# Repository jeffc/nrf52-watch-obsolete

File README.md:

# nrf52-watch

## Overview

This repo is, at present, a work-in-progress playground for designing and
building a smartwatch based on the nrf52840 microcontroller from Nordic.

## Parts

  * [MS88SF2 nRF52840 Module](https://en.minewtech.com/bluetooth-module/MS88SF2.html)
    * Main brains. nRF52840 chipset chosen for BLE capability and low (&lt;1uA)
      sleep current.
    * Chosen for ease of solderability; other modules have pads that aren't
      accessible from the sides of the module.
  * [Sharp LS013B7DH03 1.28" Memory LCD](https://www.sharpsma.com/products?sharpCategory=Memory%20LCD&p_p_parallel=0&sharpProductRecordId=1504572)
    * Always-on display.
    * Chosen for size and small power consumption.
  * [DS1302 RTC](https://datasheets.maximintegrated.com/en/ds/DS1302.pdf)
    * Realtime clock, for real timekeeping.
    * Chosen for small power consumption and library support.

## Power

  * Project is planned to be powered by a [CR3032 coin cell](https://www.digikey.com/product-detail/en/panasonic-bsg/CR3032/P121-ND/107126),
    which has a nominal capacity of 500mAh at 3V.
  * Projected lifetime is &gt;2mo, though it remains to be seen if this is
    possible

## Software

  Since there isn't code written yet, this section is largely my notepad on
  ideas and framework setup.

  * To conserve power, everything will be interrupts-driven. 
    * This includes a 60Hz toggle for the memory LCD's EXTCOMIN pin
  * PlatformIO doesn't have a builtin for the sparkfun dev board I'm using, so
    the packages/ directory and corresponding lines in platformio.ini are a
    workaround to keep the repository as portable as possible
  * A decent amount of build hackery was needed to make the native version build
    with the dummy adafruit_gfx library

## Credits / Inspiration

  * This project uses open-source code from the following projects. Licenses are
    included alongside code where applicable.
    * [Adafruit](https://github.com/adafruit/Adafruit-GFX-Library)
    * [vhervieux on github](https://github.com/croutor/Adafruit_GFX_dummy_display)
    * [jeraymond on github](https://github.com/jeraymond/pio-sparkfun_pro_nrf52840_mini-setup)
    * [UF2Conv from Microsoft](https://raw.githubusercontent.com/microsoft/uf2/master/utils/uf2conv.py)
  * This project took inspiration from these projects:
    * [Chronio](https://hackaday.io/project/12876-chronio)
    * [Samson March's Smartwatch](https://imgur.com/a/FSBwD3g)

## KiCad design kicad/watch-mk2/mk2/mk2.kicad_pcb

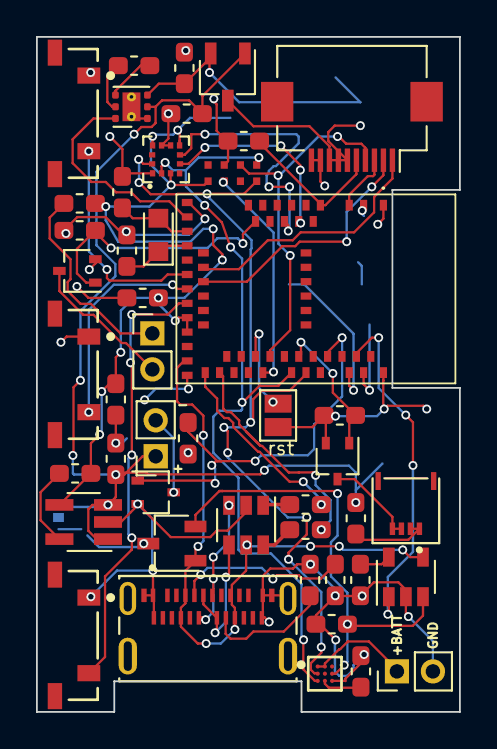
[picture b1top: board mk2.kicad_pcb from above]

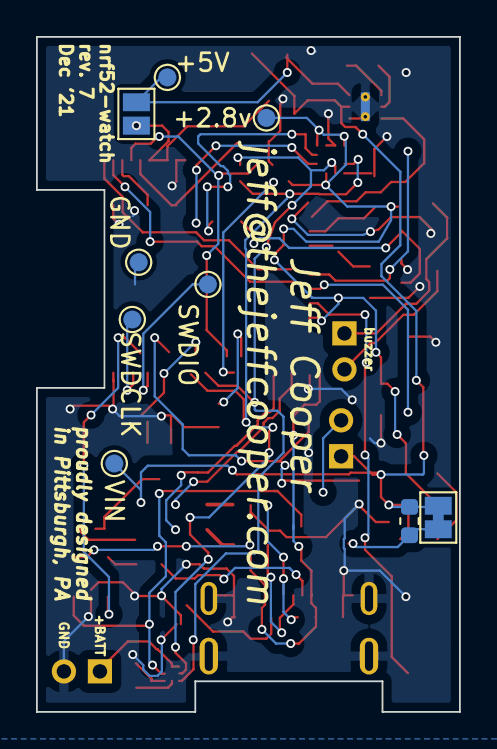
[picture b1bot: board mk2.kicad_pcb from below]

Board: 2 copper layers, 23.5 x 37.5 mm, 55 parts (9 on the bottom side), 50 nets.

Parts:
BT1: Battery_Cell; PinHeader_1x02_P2.00mm_Vertical
C1, C2: 12pF; C_0603_1608Metric_Pad1.05x0.95mm_HandSolder
C3, C7: 10uF; C_0603_1608Metric_Pad1.05x0.95mm_HandSolder
C4, C20: 4.7uF; C_0603_1608Metric_Pad1.05x0.95mm_HandSolder
C5, C6, C8: 2.2uF; C_0603_1608Metric_Pad1.05x0.95mm_HandSolder
C9: 560pF; C_0603_1608Metric_Pad1.05x0.95mm_HandSolder
C10: 0.47uF; C_0603_1608Metric_Pad1.05x0.95mm_HandSolder
D1, D2: D_Schottky_x2_KCom_AAK; TSOT-23
IC1: MDBT50Q; 113990582
IC2: M41T62LC6F; LCC90P230X50X80-8N
J1: Conn_01x10_Female; Hirose_FH12-10S-0.5SH_1x10-1MP_P0.50mm_Horizontal
J2: 2305018-2; TE_2305018-2
J3: Conn_01x02_Female; PinHeader_1x02_P2.00mm_Vertical
J4: 503480-0400; MOLEX_503480-0400
J6: Conn_01x02_Female; PinSocket_1x02_P2.00mm_Vertical
JP1, JP2: Jumper_NO_Small; SolderJumper-2_P1.3mm_Open_Pad1.0x1.5mm
JP3: Jumper_NC_Small; SolderJumper-2_P1.3mm_Bridged_Pad1.0x1.5mm
L1: 2.2uH; L_0603_1608Metric_Pad1.05x0.95mm_HandSolder
Q1, Q3, Q4: Si1308EDL; SOT-323_SC-70
R1: shunt; R_0603_1608Metric
R2, R13, R15: 100k; R_0603_1608Metric_Pad1.05x0.95mm_HandSolder
R3, R4: 27; R_0603_1608Metric_Pad1.05x0.95mm_HandSolder
R9: 2k; R_0603_1608Metric_Pad1.05x0.95mm_HandSolder
R11, R12: 5.1k; R_0603_1608Metric_Pad1.05x0.95mm_HandSolder
R14: 100; R_0603_1608Metric_Pad1.05x0.95mm_HandSolder
R16: 10; R_0603_1608Metric_Pad1.05x0.95mm_HandSolder
SW1: B5; E-Switch-TL3330AF130QG-MFG
SW2: B1; E-Switch-TL3330AF130QG-MFG
SW4: B3; E-Switch-TL3330AF130QG-MFG
TP1, TP2, TP3, TP4, TP5, TP6: TestPoint; TestPoint_Pad_D1.0mm
U1: TPS60151DRV; WSON-6-1EP_2x2mm_P0.65mm_EP1x1.6mm_ThermalVias
U2: LM3671MF-2.8_NOPB; SOT-23-5_HandSoldering
U3: MCP73831-2-OT; SOT-23-5
U4: BMA400; XDCR_BMA400
U5: TPD2S017; SOT-23-6
U6: MAX17262REWL+T; Maxim-W91G1-3-0-A-IPC_A
Y1: 32.768kHz; Crystal_SMD_2012-2Pin_2.0x1.2mm_HandSoldering

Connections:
5VREG_EN: IC1.16 (P0.27), U1.6 (ENA)
+5V: C8.1, D2.2 (A), JP1.2, TP6.1, U1.3 (VOUT)
+BATT: BT1.1 (+), U6.A1 (TH), U6.A2 (BATT)
/XL1: C1.2, IC1.17 (P0.00/XL1), Y1.2
/XL2: C2.2, IC1.18 (P0.01/XL2), Y1.1
ACCELINT1: IC1.7 (P1.14), U4.5 (INT1)
ACCELINT2: IC1.9 (P0.03), U4.6 (INT2)
BACKLIGHT: IC1.45 (P0.23), Q3.1 (G), R13.1
BATTPOW: C20.1, D1.2 (A), U3.3 (VBAT), U6.B3 (SYS)
BUTTON1: IC1.22 (P0.06), SW2.2
BUTTON3: IC1.26 (P1.09), SW4.2
BUTTON5: IC1.24 (P0.08), SW1.2
BUZZER: IC1.13 (P0.28), Q4.1 (G), R15.1
CHGNG: IC1.52 (P0.09/NFC1), U3.1 (STAT)
DISP_POWER: D2.3 (K), J1.6, J1.7, J1.8, JP1.1
FLASHLIGHT: IC1.49 (P0.25), Q1.1 (G), R2.1
GND: BT1.2 (-), C1.1, C2.1, C3.2, C4.2, C5.1, C7.2, C8.2, C9.2, C10.2, C20.2, IC1.1 (GND_1), IC1.2 (GND_2), IC1.15 (GND_3), IC1.33 (GND_4), IC1.55 (GND_5), IC2.3 (VSS), J1.9, J1.10, J2.A1 (GNDA), J2.A12 (GNDA__1), J2.B1 (GNDB), J2.B12 (GNDB__1), J2.G1 (GND), J2.G2 (GND__1), J2.S1 (SHIELD), J2.S2 (SHIELD__1), J2.S3 (SHIELD__2), J2.S4 (SHIELD__3), JP2.2, Q1.2 (S), Q3.2 (S), Q4.2 (S), R2.2, R9.2, R11.2, R12.1, R13.2, R15.2, SW1.1, SW2.1, SW4.1, TP1.1, U1.1 (GND), U1.7 (EP), U2.2 (GND), U3.2 (VSS), U4.1 (SDO), U4.8 (GNDIO), U4.9 (GND), U5.2 (GND), U6.C3 (GND)
LCD_CS: IC1.3 (P1.10), J1.3
LCD_DISP: C9.1, IC1.4 (P1.11), J1.5
unnamed: C6.1, U1.4 (CP+)
unnamed: C6.2, U1.5 (CP-)
unnamed: C10.1, U6.C2 (REG)
unnamed: D1.3 (K), JP3.2, R1.1
unnamed: IC1.34 (D-), R3.1
unnamed: IC1.35 (D+), R4.1
unnamed: J3.1, R16.2
unnamed: J3.2, Q4.3 (D)
unnamed: J4.1, J4.2, R14.2
unnamed: J4.3, J4.4, Q3.3 (D)
unnamed: J6.2, Q1.3 (D)
unnamed: L1.1, U2.5 (SW)
unnamed: R9.1, U3.5 (PROG)
unnamed: J2.B5 (CC2), R11.1
unnamed: J2.A5 (CC1), R12.2
RST: IC1.40 (P0.18/RESET), JP2.1
RTCIRQ: IC1.41 (P0.17), IC2.6 (~IRQ/OUT~)
SCL: IC1.46 (P0.22), IC2.8 (SCL), U4.12 (SCX), U6.B1 (SCL)
SDA: IC1.44 (P0.20), IC2.1 (SDA), U4.2 (SDX), U6.C1 (SDA)
SPI_CLK: IC1.21 (P0.05), J1.1
SPI_MOSI: IC1.23 (P0.07), J1.2
SQW: IC1.42 (P0.19), IC2.2 (SQW), J1.4
SWDCLK: IC1.53 (SWDCLK), TP2.1
SWDIO: IC1.51 (SWDIO), TP4.1
USB_DN: R3.2, U5.1 (CH1Out)
USB_DN_EXT: J2.A7 (DA_N), J2.B7 (DB_N), U5.3 (CH1In)
USB_DP: R4.2, U5.6 (CH2Out)
USB_DP_EXT: J2.A6 (DA_P), J2.B6 (DB_P), U5.4 (CH2Int)
VCC: C3.1, C7.1, IC1.28 (VDD), IC1.30 (VDDH), IC2.5 (VCC), L1.2, R16.1, TP3.1, U2.4 (FB), U4.3 (VDDIO), U4.7 (VDD), U4.10 (~CSB~)
VIN: C4.1, C5.2, D2.1 (A), J6.1, JP3.1, R1.2, R14.1, TP5.1, U1.2 (VIN), U2.1 (VIN), U2.3 (EN)
VUSB: D1.1 (A), IC1.32 (VBUS), J2.A4 (VBUS_A), J2.A9 (VBUS_A__1), J2.B4 (VBUS_B), J2.B9 (VBUS_B__1), U3.4 (VDD), U5.5 (VCC)

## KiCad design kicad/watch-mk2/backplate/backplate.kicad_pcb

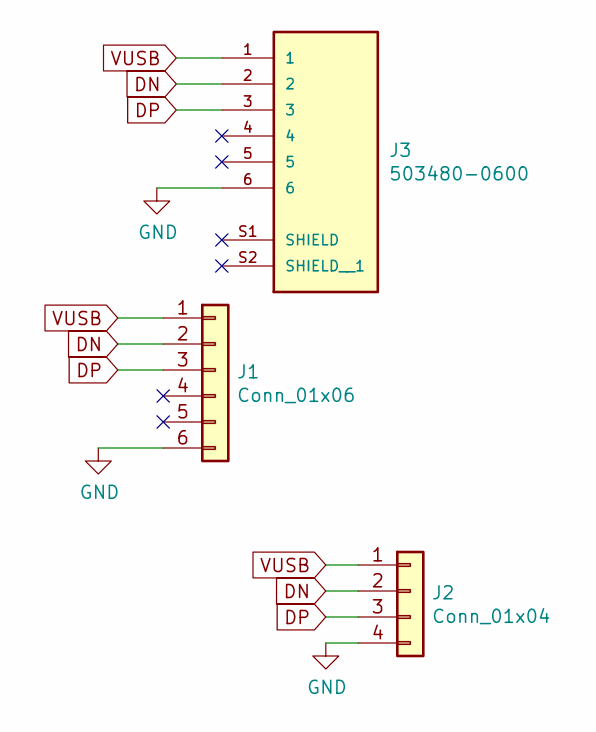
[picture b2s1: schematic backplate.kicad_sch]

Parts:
J1: Conn_01x06; ffc-strip
J2: Conn_01x04; PinHeader_1x04_P2.00mm_Vertical
J3: 503480-0600; MOLEX_503480-0600; PARTREV H

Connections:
DN: J1.2, J2.2, J3.2
DP: J1.3, J2.3, J3.3
GND: J1.6, J2.4, J3.6
VUSB: J1.1, J2.1, J3.1

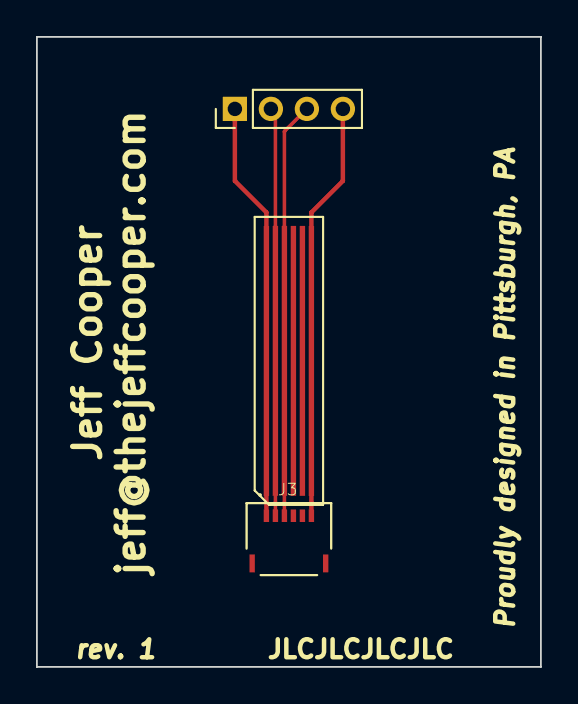
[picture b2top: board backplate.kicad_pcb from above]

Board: 2 copper layers, 28.0 x 35.0 mm, 3 parts (0 on the bottom side), 4 nets.

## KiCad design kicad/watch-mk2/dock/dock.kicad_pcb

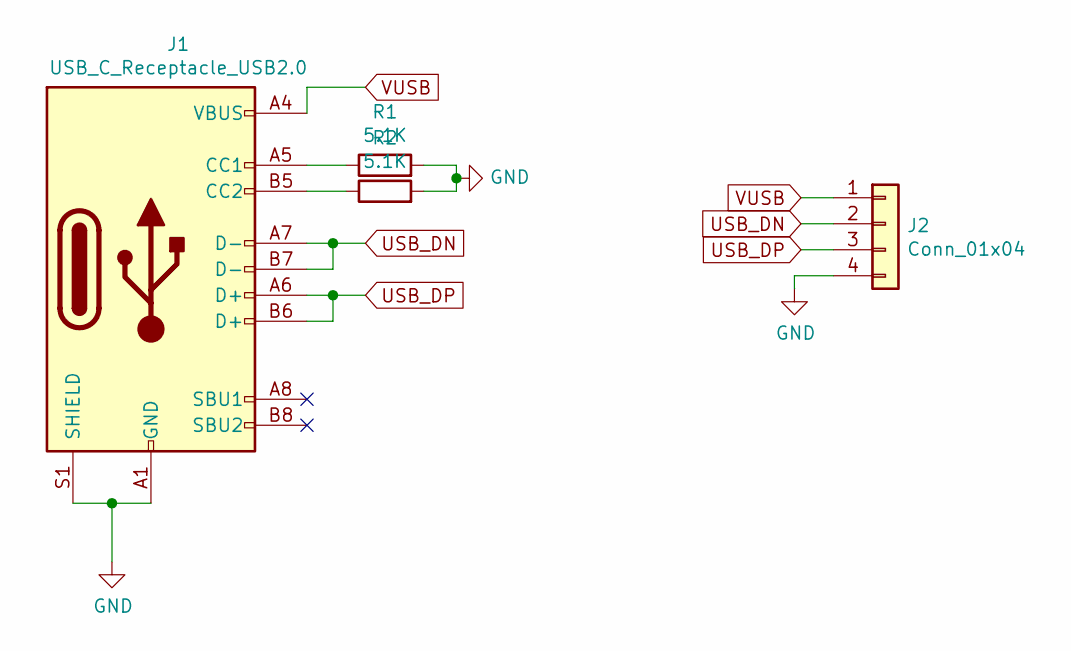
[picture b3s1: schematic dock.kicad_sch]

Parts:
J1: USB_C_Receptacle_USB2.0; USB_C_Receptacle_Palconn_UTC16-G
J2: Conn_01x04; pins
R1, R2: 5.1K; R_0603_1608Metric

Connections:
GND: J1.A1 (GND), J1.A12 (GND), J1.B1 (GND), J1.B12 (GND), J1.S1 (SHIELD), J2.4, R1.2, R2.2
unnamed: J1.A5 (CC1), R1.1
unnamed: J1.B5 (CC2), R2.1
USB_DN: J1.A7 (D-), J1.B7 (D-), J2.2
USB_DP: J1.A6 (D+), J1.B6 (D+), J2.3
VUSB: J1.A4 (VBUS), J1.A9 (VBUS), J1.B4 (VBUS), J1.B9 (VBUS), J2.1

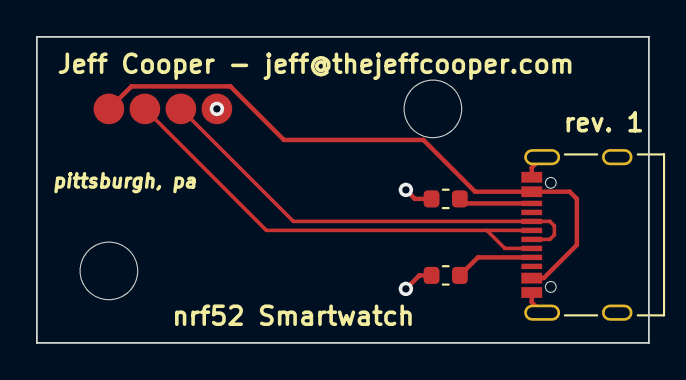
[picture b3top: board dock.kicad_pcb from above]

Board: 2 copper layers, 34.0 x 17.0 mm, 4 parts (0 on the bottom side), 6 nets.

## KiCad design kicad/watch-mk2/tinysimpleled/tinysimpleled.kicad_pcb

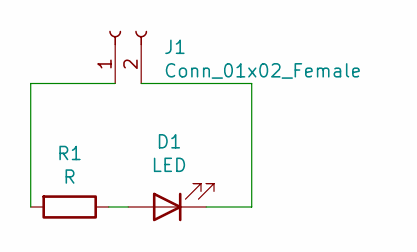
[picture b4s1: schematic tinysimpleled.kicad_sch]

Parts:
D1: LED; XM-L2
J1: Conn_01x02_Female; PinHeader_1x02_P1.00mm_Vertical
R1: R; R_2512_6332Metric

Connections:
unnamed: D1.1 (K), J1.2
unnamed: D1.2 (A), R1.1
unnamed: J1.1, R1.2

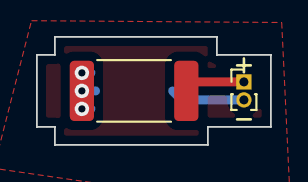
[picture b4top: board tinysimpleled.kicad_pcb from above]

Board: 2 copper layers, 13.0 x 6.0 mm, 3 parts (1 on the bottom side), 3 nets.

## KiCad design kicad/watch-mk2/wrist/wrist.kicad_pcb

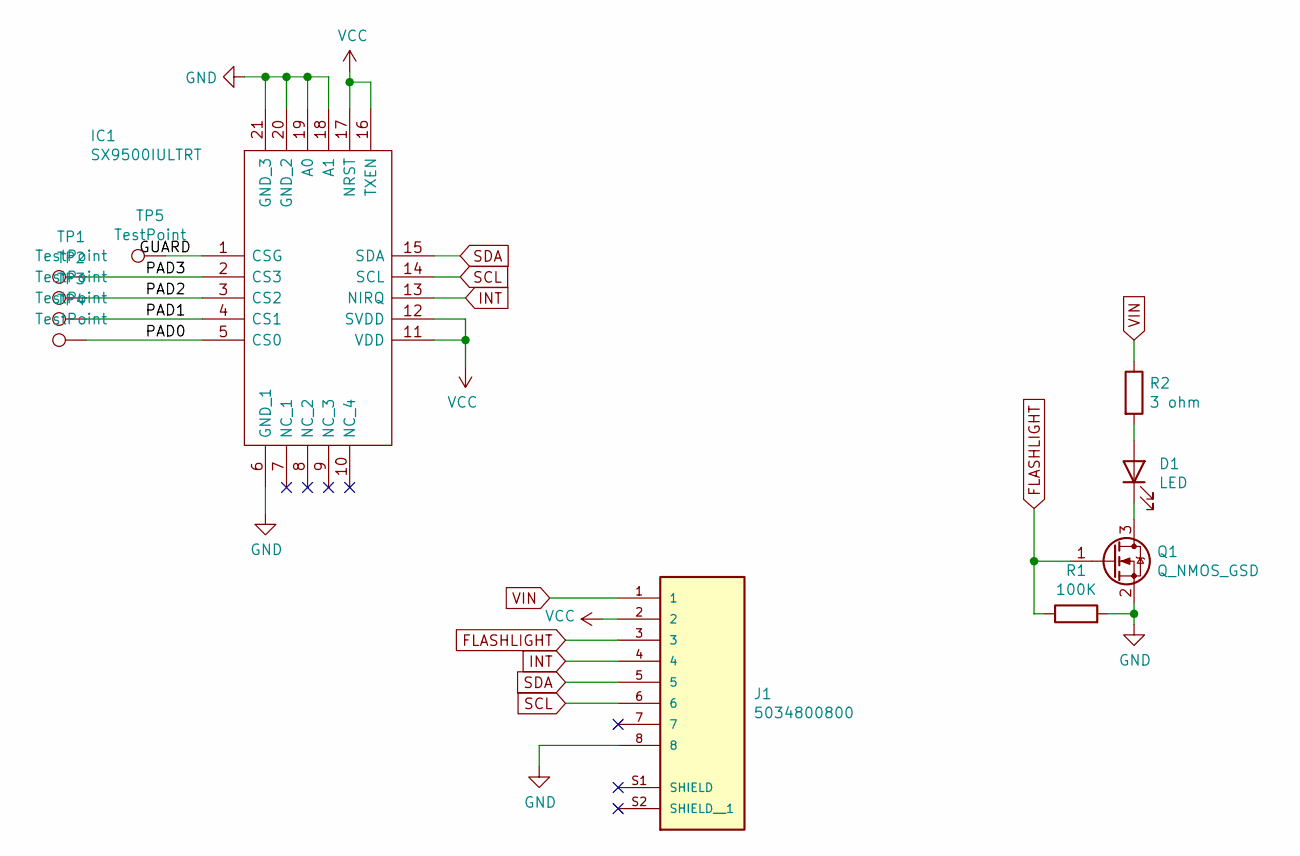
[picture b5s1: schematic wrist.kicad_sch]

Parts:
D1: LED; XM-L2
IC1: SX9500IULTRT; QFN40P300X300X60-21N; Manufacturer_Part_Number SX9500IULTRT; Mouser Part Number 947-SX9500IULTRT
J1: 5034800800; MOLEX_5034800800; PARTREV H
Q1: Q_NMOS_GSD; SOT-323_SC-70
R1: 100K; R_0603_1608Metric
R2: 3 ohm; R_2512_6332Metric
TP1, TP2, TP3, TP4, TP5: TestPoint; TestPoint_Pad_D4.0mm

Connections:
/GUARD: IC1.1 (CSG), TP5.1
/PAD0: IC1.5 (CS0), TP4.1
/PAD1: IC1.4 (CS1), TP3.1
/PAD2: IC1.3 (CS2), TP2.1
/PAD3: IC1.2 (CS3), TP1.1
FLASHLIGHT: J1.3, Q1.1 (G), R1.1
GND: IC1.6 (GND_1), IC1.18 (A1), IC1.19 (A0), IC1.20 (GND_2), IC1.21 (GND_3), J1.8, Q1.2 (S), R1.2
INT: IC1.13 (NIRQ), J1.4
unnamed: D1.1 (K), Q1.3 (D)
unnamed: D1.2 (A), R2.2
SCL: IC1.14 (SCL), J1.6
SDA: IC1.15 (SDA), J1.5
VCC: IC1.11 (VDD), IC1.12 (SVDD), IC1.16 (TXEN), IC1.17 (NRST), J1.2
VIN: J1.1, R2.1

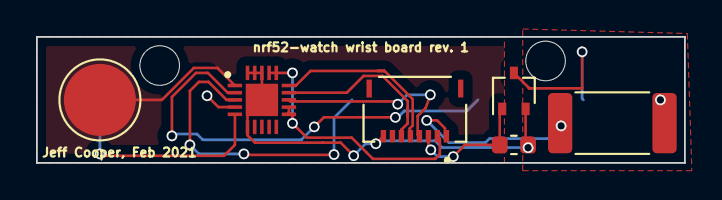
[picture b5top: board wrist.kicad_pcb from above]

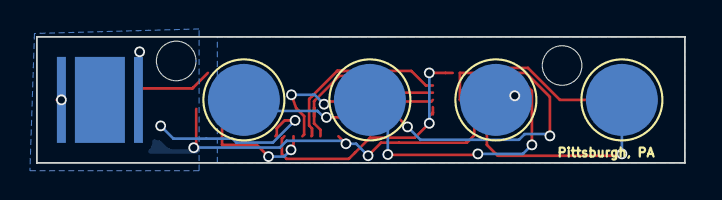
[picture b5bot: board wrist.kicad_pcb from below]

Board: 2 copper layers, 36.0 x 7.0 mm, 11 parts (5 on the bottom side), 14 nets.

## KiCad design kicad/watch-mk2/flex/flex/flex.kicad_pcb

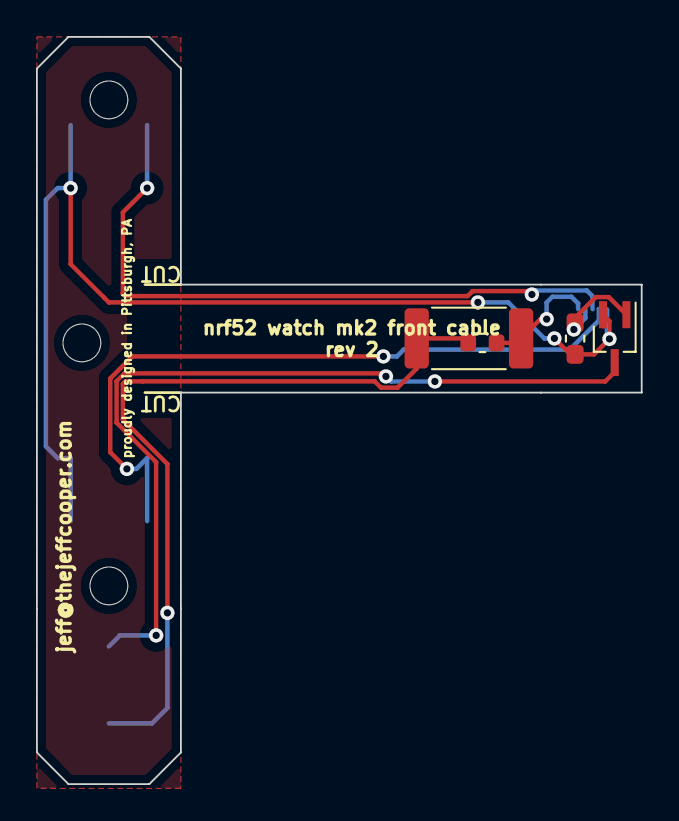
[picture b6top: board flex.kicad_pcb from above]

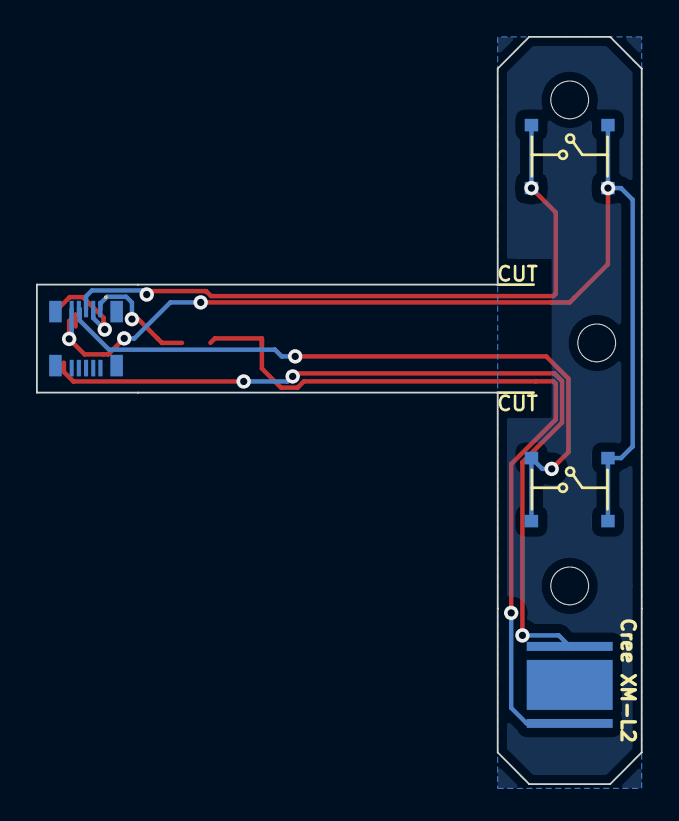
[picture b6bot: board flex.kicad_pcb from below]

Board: 2 copper layers, 33.6 x 41.5 mm, 8 parts (4 on the bottom side), 7 nets.

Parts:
D1: LED; XM-L2
P1: AXT510124; PANASONIC_AXT510124
Q1: Si1308EDL; SOT-323_SC-70_Handsoldering
R1: 100k; R_0603_1608Metric_Pad1.05x0.95mm_HandSolder
R2: 3; R_2512_6332Metric
R3: 3; R_0603_1608Metric
SW1, SW2: MCSLPT4644B4PHTR; MCSLPT4644PH

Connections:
BUTTON2: P1.5, SW1.1
BUTTON4: P1.7, SW2.1
FLASHLIGHT: P1.3, Q1.1 (G), R1.1
GND: P1.9, Q1.2 (S), R1.2, SW1.2, SW2.2
unnamed: D1.1 (K), Q1.3 (D)
unnamed: D1.2 (A), R2.2, R3.2
VIN: P1.1, R2.1, R3.1

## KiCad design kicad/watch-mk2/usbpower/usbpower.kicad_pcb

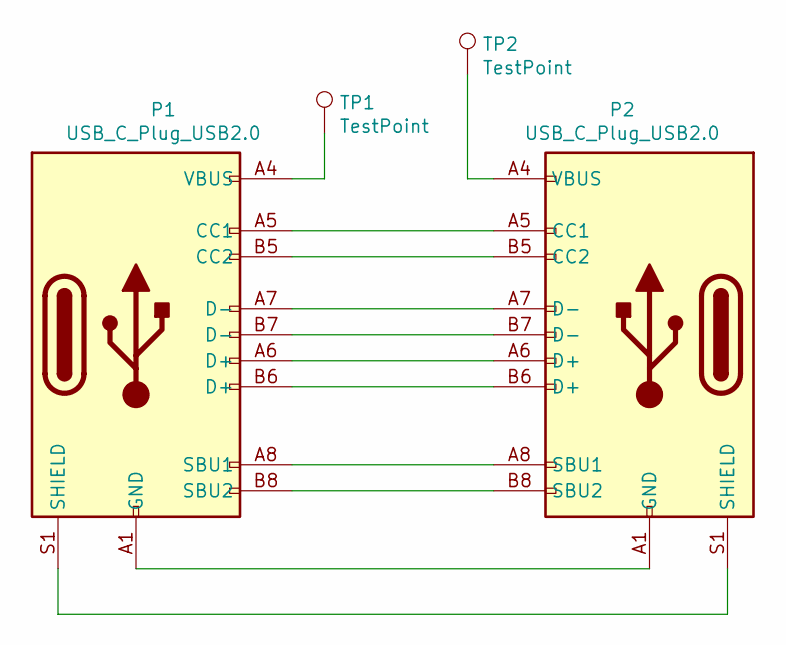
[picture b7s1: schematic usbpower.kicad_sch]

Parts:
P1, P2: USB_C_Plug_USB2.0; USB_C_Receptacle_Palconn_UTC16-G
TP1, TP2: TestPoint; TestPoint_Pad_D4.0mm

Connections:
unnamed: P1.A1 (GND), P1.A12 (GND), P1.B1 (GND), P1.B12 (GND), P2.A1 (GND), P2.A12 (GND), P2.B1 (GND), P2.B12 (GND)
unnamed: P1.A4 (VBUS), P1.A9 (VBUS), P1.B4 (VBUS), P1.B9 (VBUS), TP1.1
unnamed: P1.A5 (CC1), P2.A5 (CC1)
unnamed: P1.A6 (D+), P2.A6 (D+)
unnamed: P1.A7 (D-), P2.A7 (D-)
unnamed: P1.A8 (SBU1), P2.A8 (SBU1)
unnamed: P1.B5 (CC2), P2.B5 (CC2)
unnamed: P1.B6 (D+), P2.B6 (D+)
unnamed: P1.B7 (D-), P2.B7 (D-)
unnamed: P1.B8 (SBU2), P2.B8 (SBU2)
unnamed: P1.S1 (SHIELD), P2.S1 (SHIELD)
unnamed: P2.A4 (VBUS), P2.A9 (VBUS), P2.B4 (VBUS), P2.B9 (VBUS), TP2.1

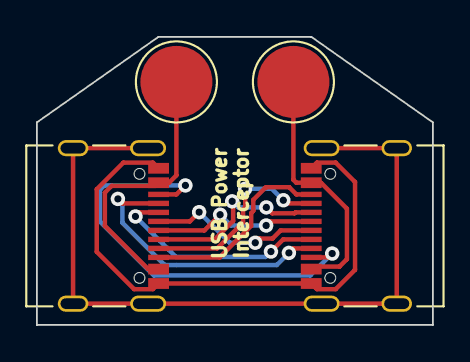
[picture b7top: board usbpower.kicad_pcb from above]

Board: 2 copper layers, 22.0 x 16.0 mm, 4 parts (0 on the bottom side), 12 nets.

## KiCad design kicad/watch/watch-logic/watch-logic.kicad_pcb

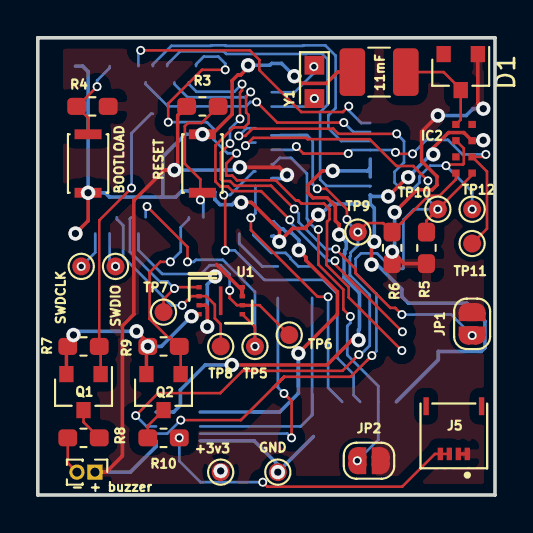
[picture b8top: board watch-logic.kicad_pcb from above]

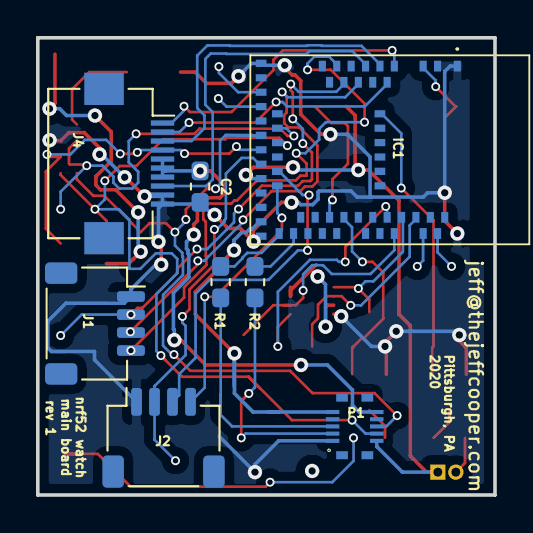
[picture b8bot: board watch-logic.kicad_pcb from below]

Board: 2 copper layers, 25.4 x 25.4 mm, 41 parts (8 on the bottom side), 39 nets.

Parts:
C1: 11mF; C_1210_3225Metric_Pad1.42x2.65mm_HandSolder
C2: 1uF; C_0603_1608Metric_Pad1.05x0.95mm_HandSolder
D1: D_Schottky; D_SOT-23_ANK
IC1: 113990582
IC2: M41T62LC6F; LCC90P230X50X80-8N
J1, J2: Conn_01x04_Female; JST_SH_SM04B-SRSS-TB_1x04-1MP_P1.00mm_Horizontal
J3: Buzzer; PinHeader_1x02_P1.00mm_Vertical
J4: Memory LCD; Hirose_FH12-10S-0.5SH_1x10-1MP_P0.50mm_Horizontal
J5: Conn_01x04_Female; MOLEX_503480-0400
JP1, JP2: Jumper_NO_Small; SolderJumper-2_P1.3mm_Open_RoundedPad1.0x1.5mm
P1: AXT610124; PANASONIC_AXT610124
Q1, Q2: DMN6140L; SOT-23
R1, R2: 27; R_0603_1608Metric_Pad1.05x0.95mm_HandSolder
R3, R4: 10k; R_0603_1608Metric_Pad1.05x0.95mm_HandSolder
R5, R6: 4k7; R_0603_1608Metric_Pad1.05x0.95mm_HandSolder
R7, R8, R9, R10: R; R_0603_1608Metric_Pad1.05x0.95mm_HandSolder
SW_BOOT1: SW_Push; SW_SPST_CK_KXT3
SW_RESET1: SW_Push; SW_SPST_CK_KXT3
TP1, TP2, TP3, TP4, TP5, TP6, TP7, TP8, TP9, TP10, TP11, TP12: TestPoint; TestPoint_Pad_D1.0mm
U1: W25X20CLUXIG; 8-USON
Y1: Crystal; Crystal_SMD_2012-2Pin_2.0x1.2mm_HandSoldering

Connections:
+3V3: D1.2, IC1.28, J3.1, J5.1, J5.2, JP1.2, JP2.2, P1.2, R3.1, R4.1, R5.1, R6.1, TP1.1, U1.3, U1.7, U1.8
+5V: C2.1, J4.5, J4.6, J4.7, P1.10
BOOTLOAD: IC1.3, R4.2, SW_BOOT1.1
BTN1: IC1.12, J1.4
BTN2: IC1.11, J1.2, JP1.1
BTN3: IC1.9, J1.3
BTN4: IC1.29, J2.4
BTN5: IC1.27, J2.3
BTN6: IC1.26, J2.2, JP2.1
BUZZER: IC1.56, Q1.1, R7.2
EXTMODE: IC1.8, J4.8
FLASH_CLK: IC1.48, TP6.1, U1.6
FLASH_CS: IC1.49, TP7.1, U1.1
FLASH_DI: IC1.47, TP5.1, U1.5
FLASH_DO: IC1.50, TP8.1, U1.2
FRONTLIGHT: IC1.42, Q2.1, R9.2
GND: C1.2, C2.2, IC1.1, IC1.2, IC1.15, IC1.33, IC1.55, IC2.3, J1.1, J2.1, J4.9, J4.10, P1.1, Q1.2, Q2.2, R7.1, R9.1, SW_BOOT1.2, SW_RESET1.2, TP2.1, U1.4
LCD_CLK: IC1.4, J4.1
LCD_CS: IC1.6, J4.3
LCD_MOSI: IC1.5, J4.2
unnamed: C1.1, D1.1, IC2.5
unnamed: IC1.17, Y1.1
unnamed: IC1.18, Y1.2
unnamed: IC1.34, R1.2
unnamed: IC1.35, R2.2
unnamed: J3.2, R8.1
unnamed: J5.3, J5.4, R10.1
unnamed: Q1.3, R8.2
unnamed: Q2.3, R10.2
RST: IC1.40, R3.2, SW_RESET1.1
RTC_IRQ: IC1.21, IC2.6, TP12.1
SCL: IC1.22, IC2.8, P1.6, R6.2, TP9.1
SDA: IC1.23, IC2.1, P1.4, R5.2, TP10.1
SQW: IC1.24, IC2.2, J4.4, TP11.1
SWDCLK: IC1.53, TP3.1
SWDIO: IC1.51, TP4.1
USB_DN: P1.5, R1.1
USB_DP: P1.3, R2.1
VBUS: IC1.32, P1.9

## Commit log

2020-02-08 initial commit. messing with library management
2020-02-08 add a test source file
2020-02-09 fixed library issues, can now compile with dummy graphics lib
2020-02-10 Fixed library stuff for real, undid submodule trickery
2020-02-10 add a readme
2020-02-10 added a first crack at a logging library
2020-02-10 added logging lib.
    haven't tested it on embedded yet
2020-02-10 remove .travis.yml
2020-02-10 Add platform-independent graphics shim
2020-02-13 add first round of pcb files
2020-02-14 Second rev of schematic. Not yet routed.
2020-02-15 routed board rev2
2020-02-15 added voltage divider for battery reading
2020-02-15 some work on main_nrf52
2020-02-15 Patched Adafruit_GFX_dummy_display to allow for displays larger than 255x255
2020-02-16 add graphics lib resolution change
2020-02-16 Add some RTC scaffold and a seven-segment font
2020-02-16 add day of week to rtc structs
2020-02-16 Add qwiic jumpers for accessory ports
2020-02-17 add button panel, finish silk for main pcb
2020-02-18 checkpoint before redoing schematic
2020-02-18 add 3d files for most connectors, start on usbc breakout
2020-02-18 un-derped pcb references
2020-02-18 re-add 3d files for footprint
2020-02-19 add bignum, tweaks to graphics
2020-02-19 add basic bignum. probably should be boosted to 16bits
2020-02-19 add scaling for big numbers. too square, probably
2020-02-19 native now showing a very bad clock
2020-02-21 checkpoint before retooling board...again.
2020-02-23 Add modified version of Adafruit GFX library to work with 1.8" display (9 bits of address)
2020-02-23 add clearbuffer() method to adafruit_sharpmem_modified
2020-02-23 checkpoint
2020-02-25 finished redesign of main board
2020-02-25 finish gerbers for three internal boards
2020-02-25 pcbs ordered :)
2020-05-02 snapshot for upload to github, now that copyrights are cleared
2020-07-22 add mk2 schematics
2020-08-21 add rev2mk2
2020-08-23 commit rev3
2020-09-02 add rev2 of flex cable
2021-02-07 schematic checkpoint
